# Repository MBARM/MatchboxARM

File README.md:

MatchboxARM
===========

CD content for MatchboxARM STM32F103C8T6 board and MatchboxARM robotic platform
    
    ## Software and design by Nedelcu Bogdan Sebastian.

To compile examplex for CooCox:
    * download CooCox
	* copy all "workspace" content from CD to "C:\CooCox\CoIDE\workspace"
	* install gcc-arm-none-eabi-4_6-2012q2-20120614.exe
Open CoIDE. In the menu -> project -> select toolchain path
set the pat to armgcc( C:\Program Files (x86)\GNU Tools ARM Embedded\4.6 2012q2\bin ).

To compile examples for KEIL, download KEIL evaluation version with 32kb limit.

The bootloader sources are in KEIL directory.

Most of the examples need NEED USB-TTL adapter to get the feedback.
You need to connect the adapter like this:

USB-TTL ADAPTER            MatchboxARM
    TX           ->         RX (PA10)
    RX           ->         TX (PA9)
    GND          ->         GND 

The setting on the PC side for the serial port are:
	   BAUD RATE : 38400 
	   DATA BITS : 8
	   STOP BITS : 1
	      PARITY : NONE
	FLOW CONTROL : NONE

The termite is a free serial terminal for Windows.

The work is still in progress for Linux.

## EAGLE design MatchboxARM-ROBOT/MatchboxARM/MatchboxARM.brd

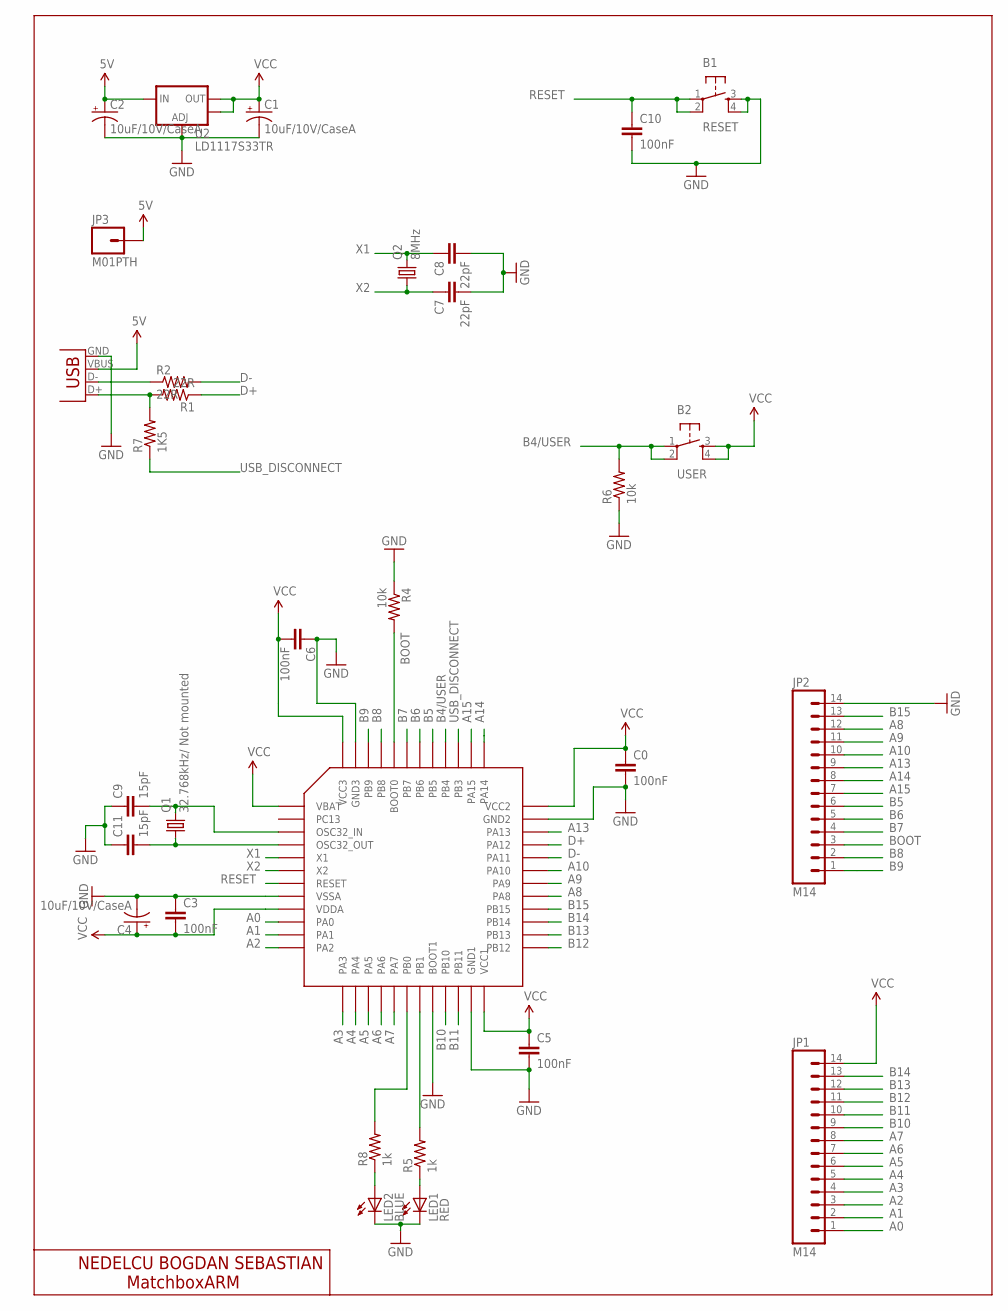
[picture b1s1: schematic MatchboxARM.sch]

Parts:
B1: RESET; TACTILE_SWITCH_SMD
B2: USER; TACTILE_SWITCH_SMD
C0, C3, C5, C6, C10: 100nF; 0603-CAP
C1, C2, C4: 10uF/10V/CaseA; EIA3216
C7, C8: 22pF; 0603-CAP
C9, C11: 15pF; 0603-CAP
JP1, JP2: M14; 1X14
JP3: M01PTH; 1X01
LED1: RED; LED-0603
LED2: BLUE; LED-0603
Q1: 32.768kHz/ Not mounted; TC26V
Q2: 8MHz; CTS406
R1, R2: 22R; 0603-RES
R4, R6: 10k; 0603-RES
R5, R8: 1k; 0603-RES
R7: 1K5; 0603-RES
U1: STM32F103CBT6; STM32F103CXT6
U2: LD1117S33TR; SOT223
USB1: miniUSBSMD; USB-MINIB

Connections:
5V: C2.A (+), JP3.1, U2.3 (IN), USB1.VBUS
A0: JP1.1, U1.10 (PA0)
A1: JP1.2, U1.11 (PA1)
A2: JP1.3, U1.12 (PA2)
A3: JP1.4, U1.13 (PA3)
A4: JP1.5, U1.14 (PA4)
A5: JP1.6, U1.15 (PA5)
A6: JP1.7, U1.16 (PA6)
A7: JP1.8, U1.17 (PA7)
A8: JP2.12, U1.29 (PA8)
A9: JP2.11, U1.30 (PA9)
A10: JP2.10, U1.31 (PA10)
A13: JP2.9, U1.34 (PA13)
A14: JP2.8, U1.37 (PA14)
A15: JP2.7, U1.38 (PA15)
B4/USER: B2.1, B2.2, R6.2, U1.40 (PB4)
B5: JP2.6, U1.41 (PB5)
B6: JP2.5, U1.42 (PB6)
B7: JP2.4, U1.43 (PB7)
B8: JP2.2, U1.45 (PB8)
B9: JP2.1, U1.46 (PB9)
B10: JP1.9, U1.21 (PB10)
B11: JP1.10, U1.22 (PB11)
B12: JP1.11, U1.25 (PB12)
B13: JP1.12, U1.26 (PB13)
B14: JP1.13, U1.27 (PB14)
B15: JP2.13, U1.28 (PB15)
BOOT: JP2.3, R4.2, U1.44 (BOOT0)
D+: R1.1, U1.33 (PA12)
D-: R2.2, U1.32 (PA11)
GND: B1.3, B1.4, C0.2, C1.C (-), C2.C (-), C3.1, C4.C (-), C5.2, C6.1, C7.2, C8.2, C9.1, C10.2, C11.1, JP2.14, LED1.C, LED2.C, R4.1, R6.1, U1.8 (VSSA), U1.20 (BOOT1), U1.23 (GND1), U1.35 (GND2), U1.47 (GND3), U2.1 (ADJ), USB1.GND
unnamed: R5.2, U1.19 (PB1)
unnamed: LED2.A, R8.1
unnamed: LED1.A, R5.1
unnamed: R8.2, U1.18 (PB0)
unnamed: C9.2, Q1.2, U1.3 (OSC32_IN)
unnamed: C11.2, Q1.1, U1.4 (OSC32_OUT)
unnamed: R2.1, USB1.D-
unnamed: R1.2, R7.2, USB1.D+
RESET: B1.1, B1.2, C10.1, U1.7 (RESET)
USB_DISCONNECT: R7.1, U1.39 (PB3)
VCC: B2.3, B2.4, C0.1, C1.A (+), C3.2, C4.A (+), C5.1, C6.2, JP1.14, U1.1 (VBAT), U1.9 (VDDA), U1.24 (VCC1), U1.36 (VCC2), U1.48 (VCC3), U2.2 (OUT), U2.4 (OUT)
X1: C8.1, Q2.3 (2), U1.5 (X1)
X2: C7.1, Q2.1, U1.6 (X2)

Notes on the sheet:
NEDELCU BOGDAN SEBASTIAN
MatchboxARM

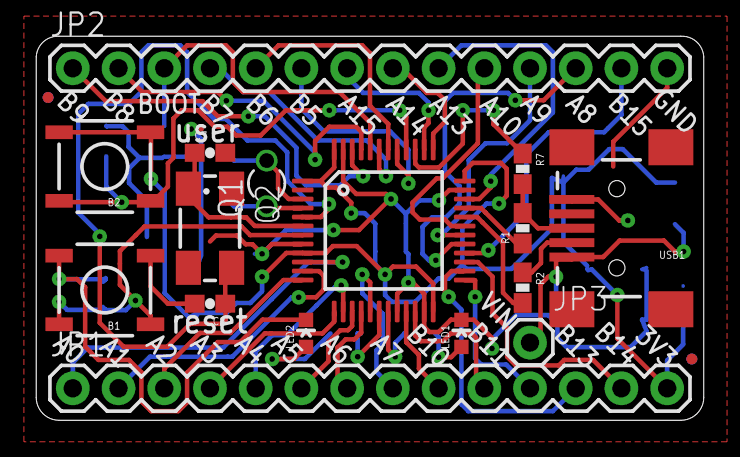
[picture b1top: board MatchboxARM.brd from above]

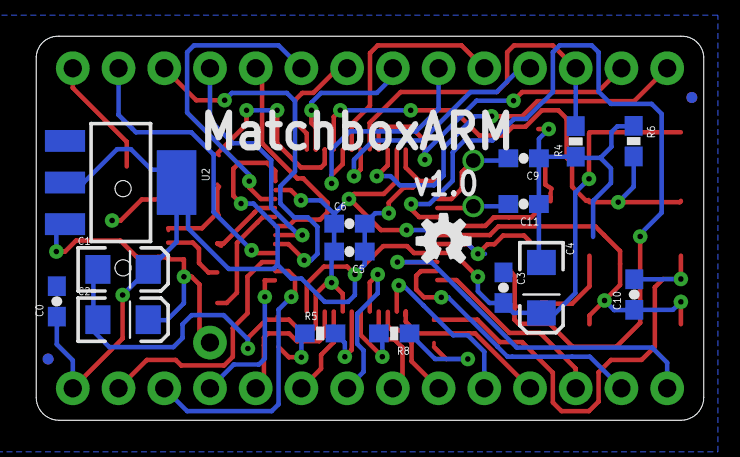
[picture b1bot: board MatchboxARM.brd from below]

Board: 2 copper layers, 37.1 x 21.3 mm, 33 parts (16 on the bottom side), 44 nets.

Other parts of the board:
U3: CREATIVE_COMMONS
U$4: OSHW-LOGOS; OSHW-LOGO-S

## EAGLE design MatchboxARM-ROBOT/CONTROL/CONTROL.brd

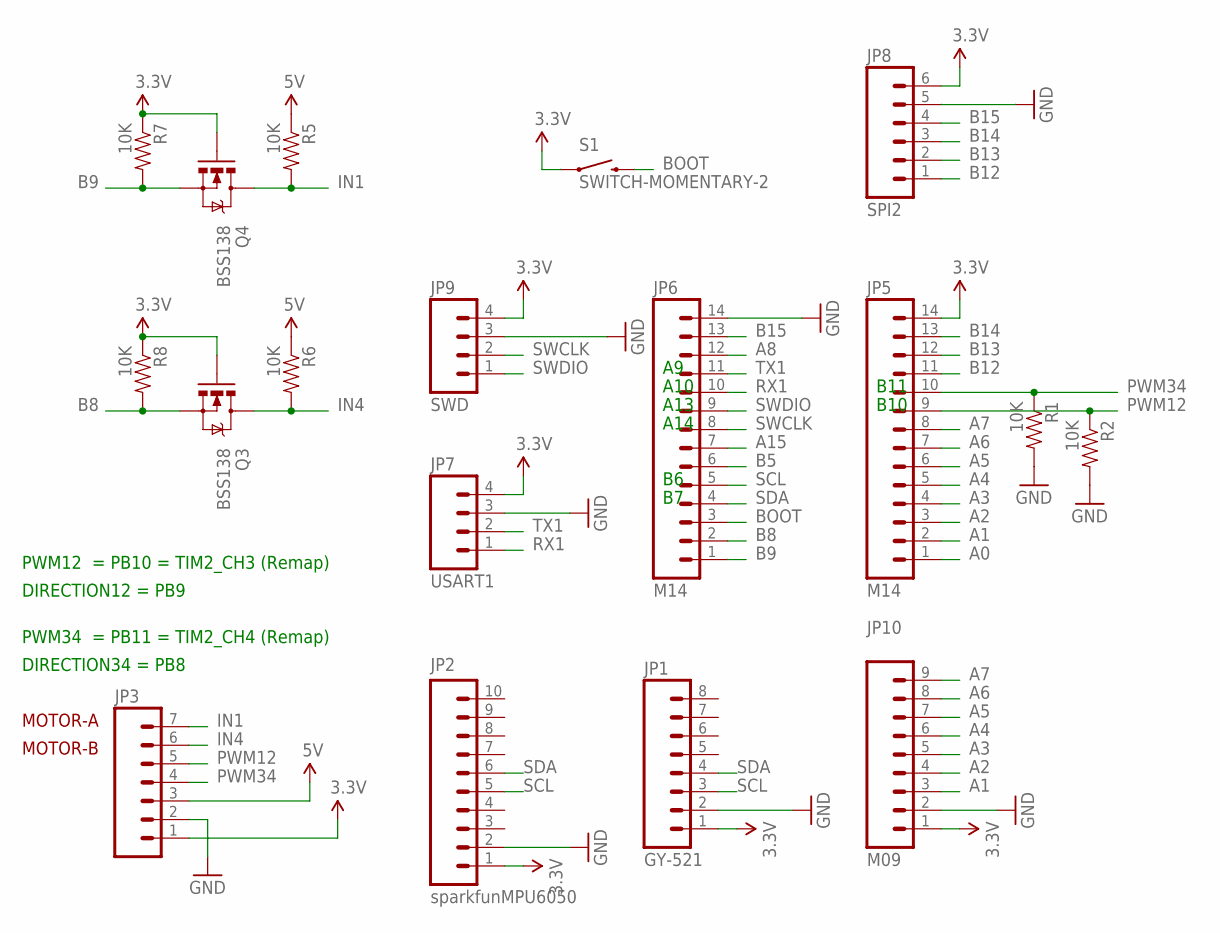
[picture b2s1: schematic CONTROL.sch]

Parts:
JP1: GY-521; 1X08
JP2: sparkfunMPU6050; 1X10
JP3: M07LONGPADS; 1X07_LONGPADS
JP5, JP6: M14; 1X14
JP7: USART1; 1X04
JP8: SPI2; 1X06
JP9: SWD; 1X04
JP10: M09; 1X09
Q3, Q4: BSS138; SOT23-3
R1, R2, R5, R6, R7, R8: 10K; 0805
S1: SWITCH-MOMENTARY-2; TACTILE_SWITCH_TALL

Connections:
3.3V: JP1.1, JP2.1, JP3.1, JP5.14, JP7.4, JP8.6, JP9.4, JP10.1, Q3.1 (G), Q4.1 (G), R7.1, R8.1, S1.A2 (1)
5V: JP3.3, R5.1, R6.1
A0: JP5.1
A1: JP5.2, JP10.3
A2: JP5.3, JP10.4
A3: JP5.4, JP10.5
A4: JP5.5, JP10.6
A5: JP5.6, JP10.7
A6: JP5.7, JP10.8
A7: JP5.8, JP10.9
A8: JP6.12
A15: JP6.7
B5: JP6.6
B8: JP6.2, Q3.2 (S), R8.2
B9: JP6.1, Q4.2 (S), R7.2
B12: JP5.11, JP8.1
B13: JP5.12, JP8.2
B14: JP5.13, JP8.3
B15: JP6.13, JP8.4
BOOT: JP6.3, S1.B2 (2)
GND: JP1.2, JP2.2, JP3.2, JP6.14, JP7.3, JP8.5, JP9.3, JP10.2, R1.2, R2.2
IN1: JP3.7, Q4.3 (D), R5.2
IN4: JP3.6, Q3.3 (D), R6.2
PWM12: JP3.5, JP5.9, R2.1
PWM34: JP3.4, JP5.10, R1.1
RX1: JP6.10, JP7.1
SCL: JP1.3, JP2.5, JP6.5
SDA: JP1.4, JP2.6, JP6.4
SWCLK: JP6.8, JP9.2
SWDIO: JP6.9, JP9.1
TX1: JP6.11, JP7.2

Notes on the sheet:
MOTOR-A
MOTOR-B
PWM12 = PB10 = TIM2_CH3 (Remap)
PWM34 = PB11 = TIM2_CH4 (Remap)
A13
A14
A10
DIRECTION12 = PB9
DIRECTION34 = PB8
B10
B11

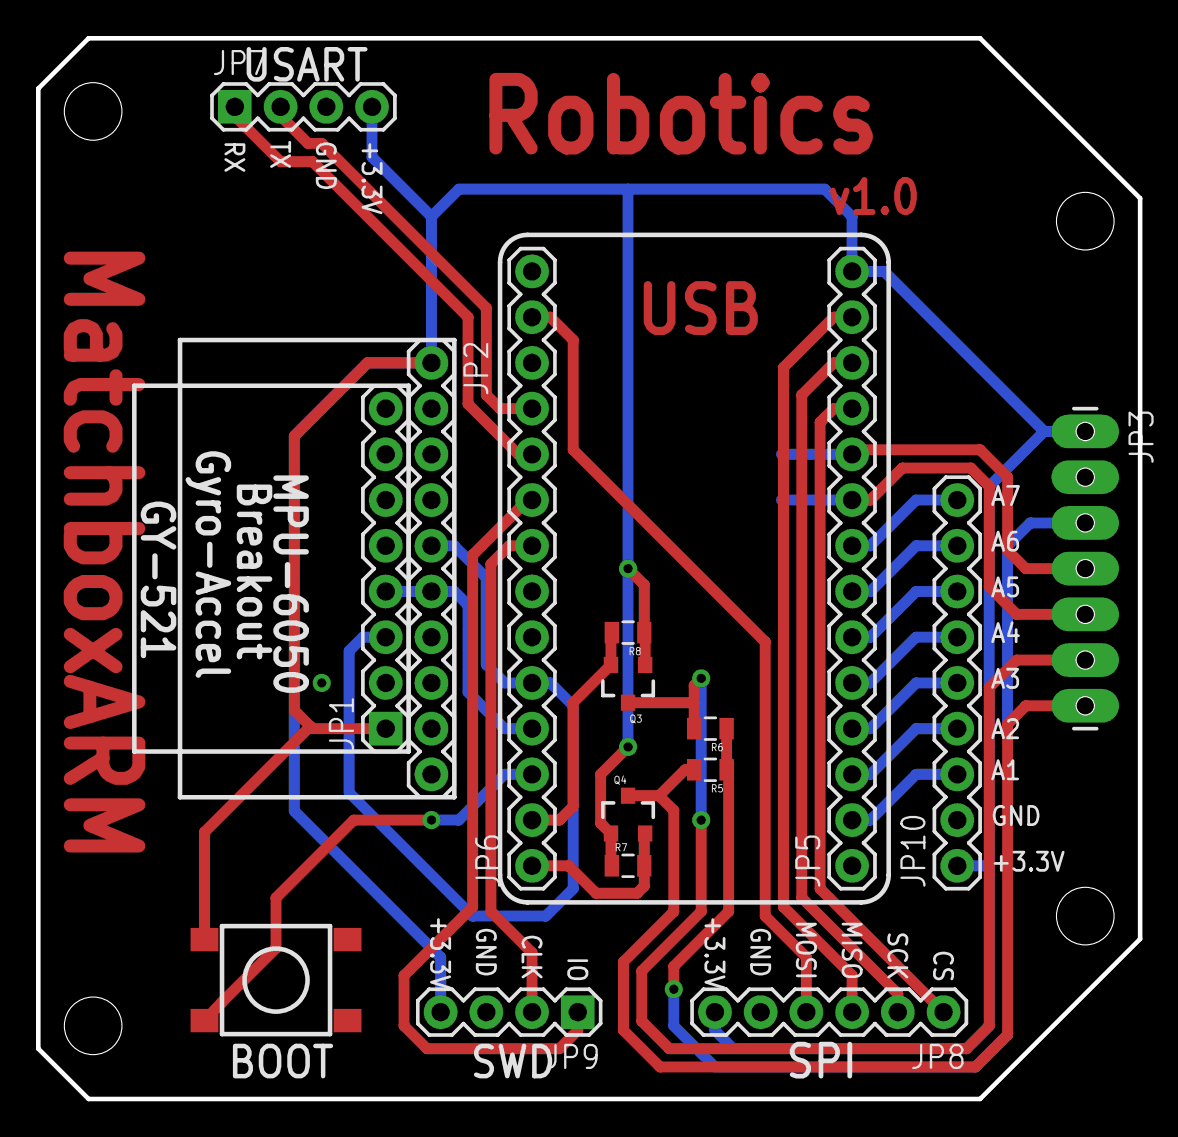
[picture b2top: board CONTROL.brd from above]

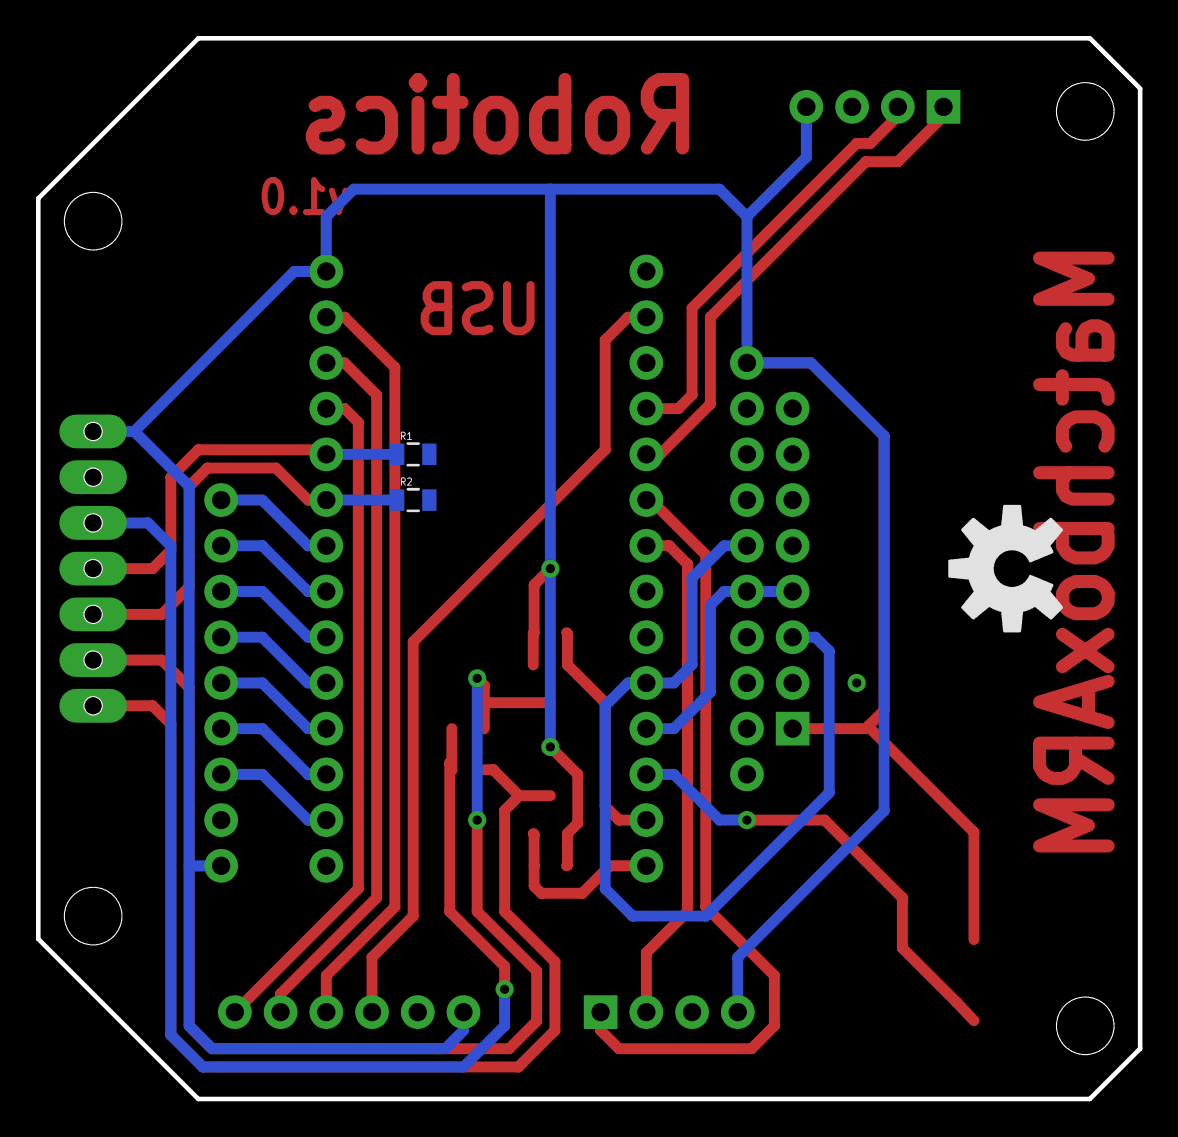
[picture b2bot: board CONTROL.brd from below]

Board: 2 copper layers, 61.2 x 58.9 mm, 20 parts (3 on the bottom side), 27 nets.

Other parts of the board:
U$1: OSHW-LOGO-L
U$2: CREATIVE_COMMONS

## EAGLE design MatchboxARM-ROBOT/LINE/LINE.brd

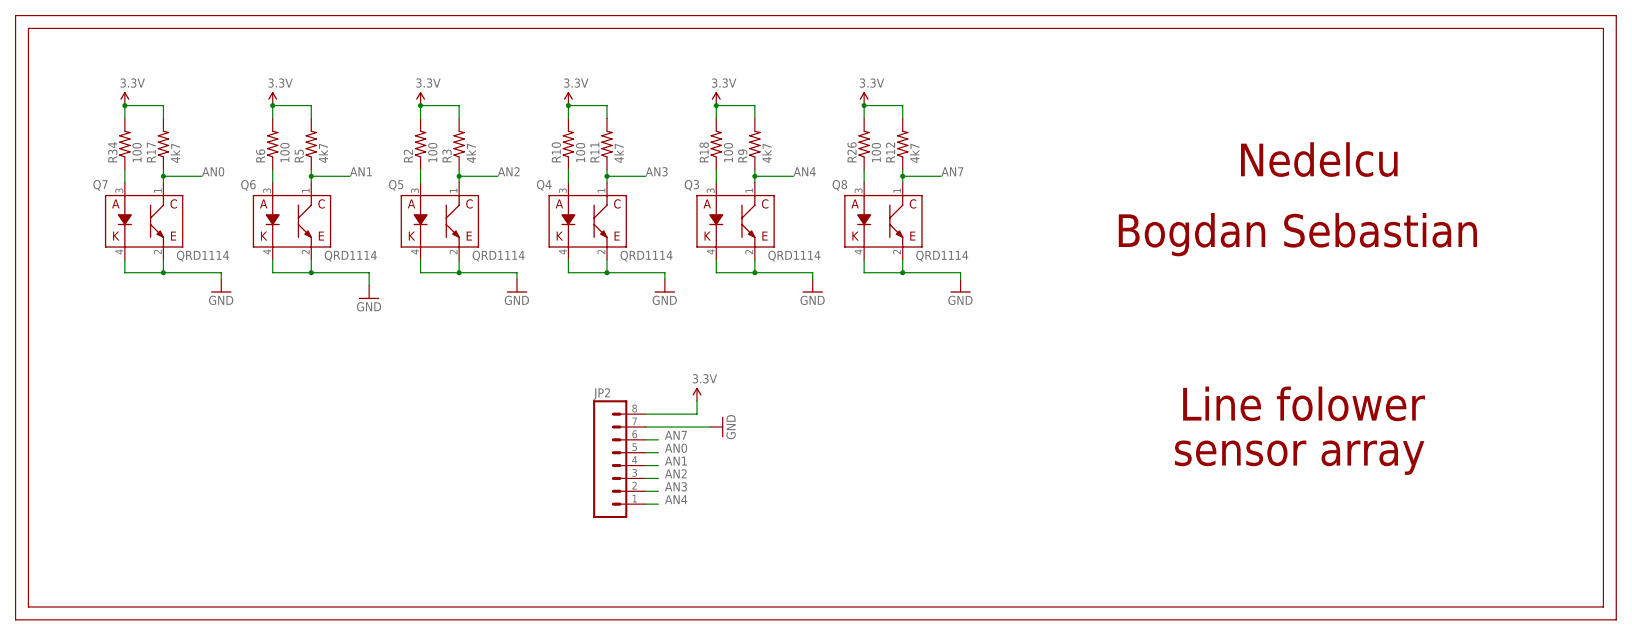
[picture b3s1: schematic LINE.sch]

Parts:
JP2: M081X08; 1X08
Q3, Q4, Q5, Q6, Q7, Q8: QRD1114
R2, R6, R10, R18, R26, R34: 100; 0805
R3, R5, R9, R11, R12, R17: 4k7; 0805

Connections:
3.3V: JP2.8, R2.2, R3.2, R5.2, R6.2, R9.2, R10.2, R11.2, R12.2, R17.2, R18.2, R26.2, R34.2
AN0: JP2.5, Q7.1 (E), R17.1
AN1: JP2.4, Q6.1 (E), R5.1
AN2: JP2.3, Q5.1 (E), R3.1
AN3: JP2.2, Q4.1 (E), R11.1
AN4: JP2.1, Q3.1 (E), R9.1
AN7: JP2.6, Q8.1 (E), R12.1
GND: JP2.7, Q3.2 (C), Q3.4 (K), Q4.2 (C), Q4.4 (K), Q5.2 (C), Q5.4 (K), Q6.2 (C), Q6.4 (K), Q7.2 (C), Q7.4 (K), Q8.2 (C), Q8.4 (K)
unnamed: Q8.3 (A), R26.1
unnamed: Q7.3 (A), R34.1
unnamed: Q6.3 (A), R6.1
unnamed: Q5.3 (A), R2.1
unnamed: Q3.3 (A), R18.1
unnamed: Q4.3 (A), R10.1

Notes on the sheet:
Nedelcu
Bogdan Sebastian
Line folower
sensor array

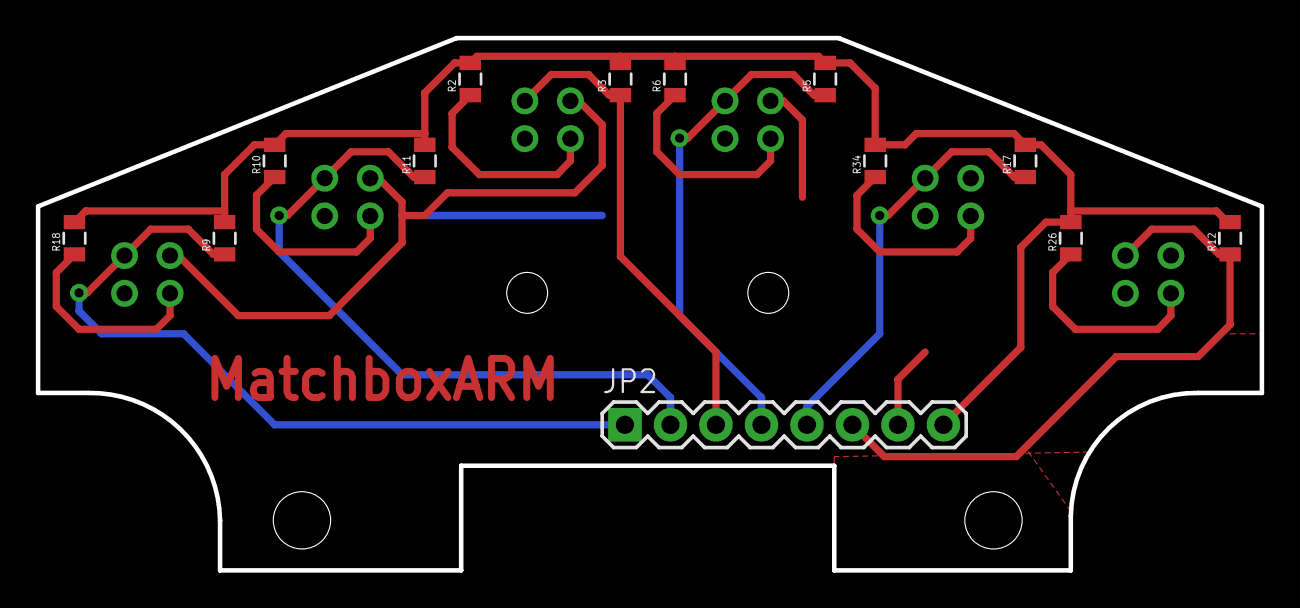
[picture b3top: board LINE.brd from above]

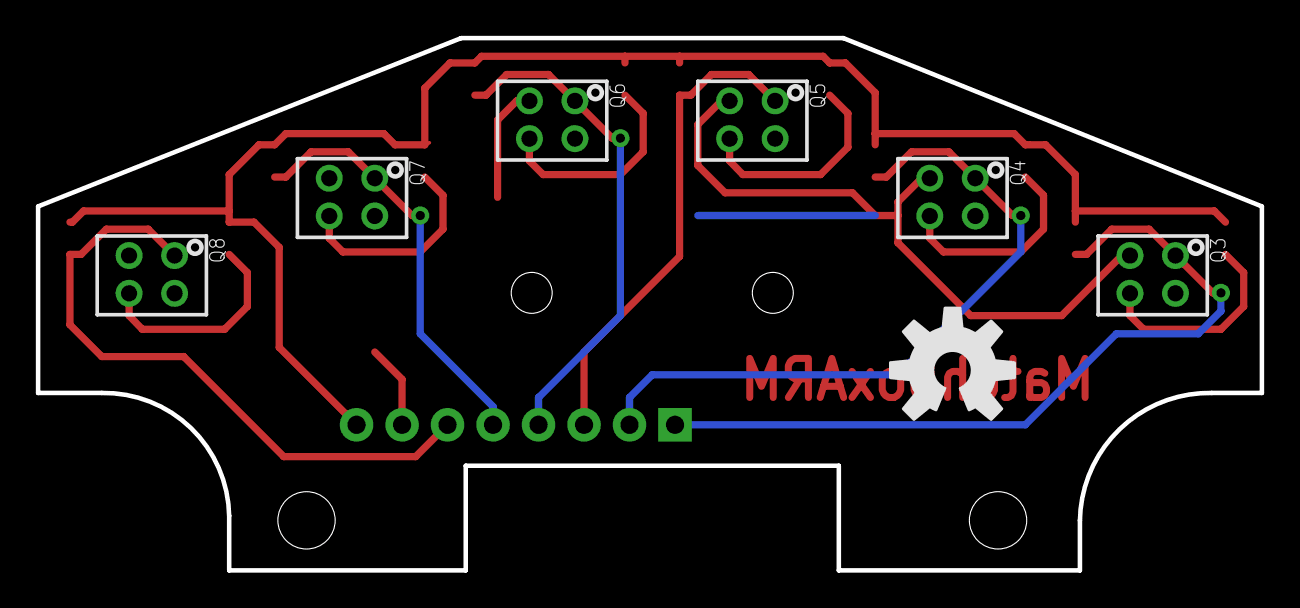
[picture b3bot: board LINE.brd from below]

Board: 2 copper layers, 68.3 x 29.7 mm, 21 parts (7 on the bottom side), 14 nets.

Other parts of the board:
U$1: CREATIVE_COMMONS
U$2: OSHW-LOGO-L

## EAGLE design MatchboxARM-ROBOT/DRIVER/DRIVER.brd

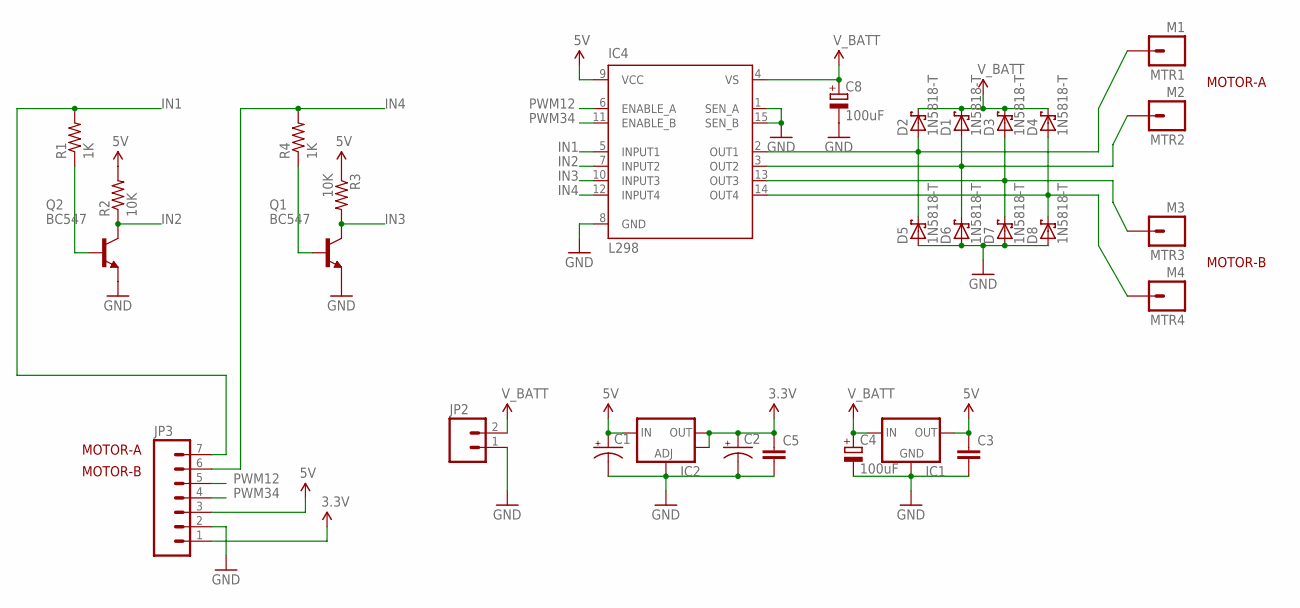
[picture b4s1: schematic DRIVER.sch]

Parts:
C1, C2: CAP_POL1206-KIT; EIA3216-KIT
C3: CAPPTH; CAP-PTH-SMALL
C4, C8: 100uF; E2,5-5
C5: CAP0805; 0805
D1, D2, D3, D4, D5, D6, D7, D8: 1N5818-T; DO41-7.6
IC1: V_REG_78XX-TO-220; TO-220-ALT
IC2: V_REG_LM1117SOT223; SOT223
IC4: L298; MULTIWATT-15
JP2: M02LOCK_LONGPADS; 1X02_LOCK_LONGPADS
JP3: M07LONGPADS; 1X07_LONGPADS
MTR1: M1; 1X01_LONGPAD
MTR2: M2; 1X01_LONGPAD
MTR3: M3; 1X01_LONGPAD
MTR4: M4; 1X01_LONGPAD
Q1, Q2: BC547; TO92
R1, R4: 1K; 0805
R2, R3: 10K; 0805

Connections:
3.3V: C2.A (+), C5.1, IC2.2 (OUT), IC2.4 (OUT), JP3.1
5V: C1.A (+), C3.1, IC1.OUT, IC2.3 (IN), IC4.9 (VCC), JP3.3, R2.2, R3.1
GND: C1.C (-), C2.C (-), C3.2, C4.-, C5.2, C8.-, D5.A, D6.A, D7.A, D8.A, IC1.GND, IC2.1 (ADJ), IC4.1 (SEN_A), IC4.8 (GND), IC4.15 (SEN_B), JP2.1, JP3.2, Q1.1 (E), Q2.1 (E)
IN1: IC4.5 (INPUT1), JP3.7, R1.2
IN2: IC4.7 (INPUT2), Q2.3 (C), R2.1
IN3: IC4.10 (INPUT3), Q1.3 (C), R3.2
IN4: IC4.12 (INPUT4), JP3.6, R4.2
unnamed: Q2.2 (B), R1.1
unnamed: Q1.2 (B), R4.1
unnamed: D2.A, D5.C, IC4.2 (OUT1), MTR1.1
unnamed: D1.A, D6.C, IC4.3 (OUT2), MTR2.1
unnamed: D3.A, D7.C, IC4.13 (OUT3), MTR3.1
unnamed: D4.A, D8.C, IC4.14 (OUT4), MTR4.1
PWM12: IC4.6 (ENABLE_A), JP3.5
PWM34: IC4.11 (ENABLE_B), JP3.4
V_BATT: C4.+, C8.+, D1.C, D2.C, D3.C, D4.C, IC1.IN, IC4.4 (VS), JP2.2

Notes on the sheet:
MOTOR-A
MOTOR-B

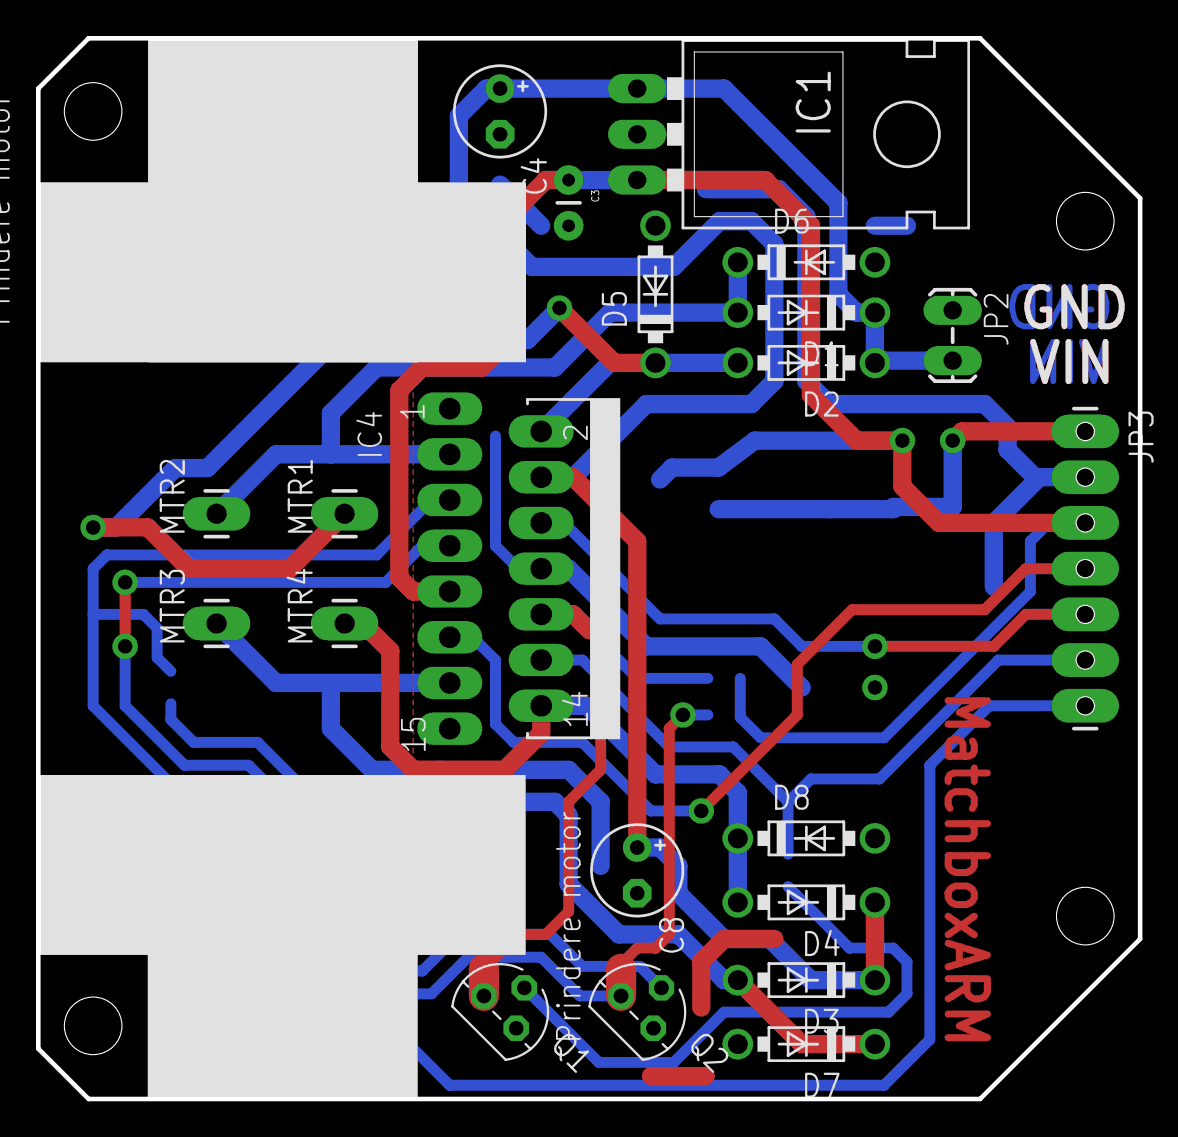
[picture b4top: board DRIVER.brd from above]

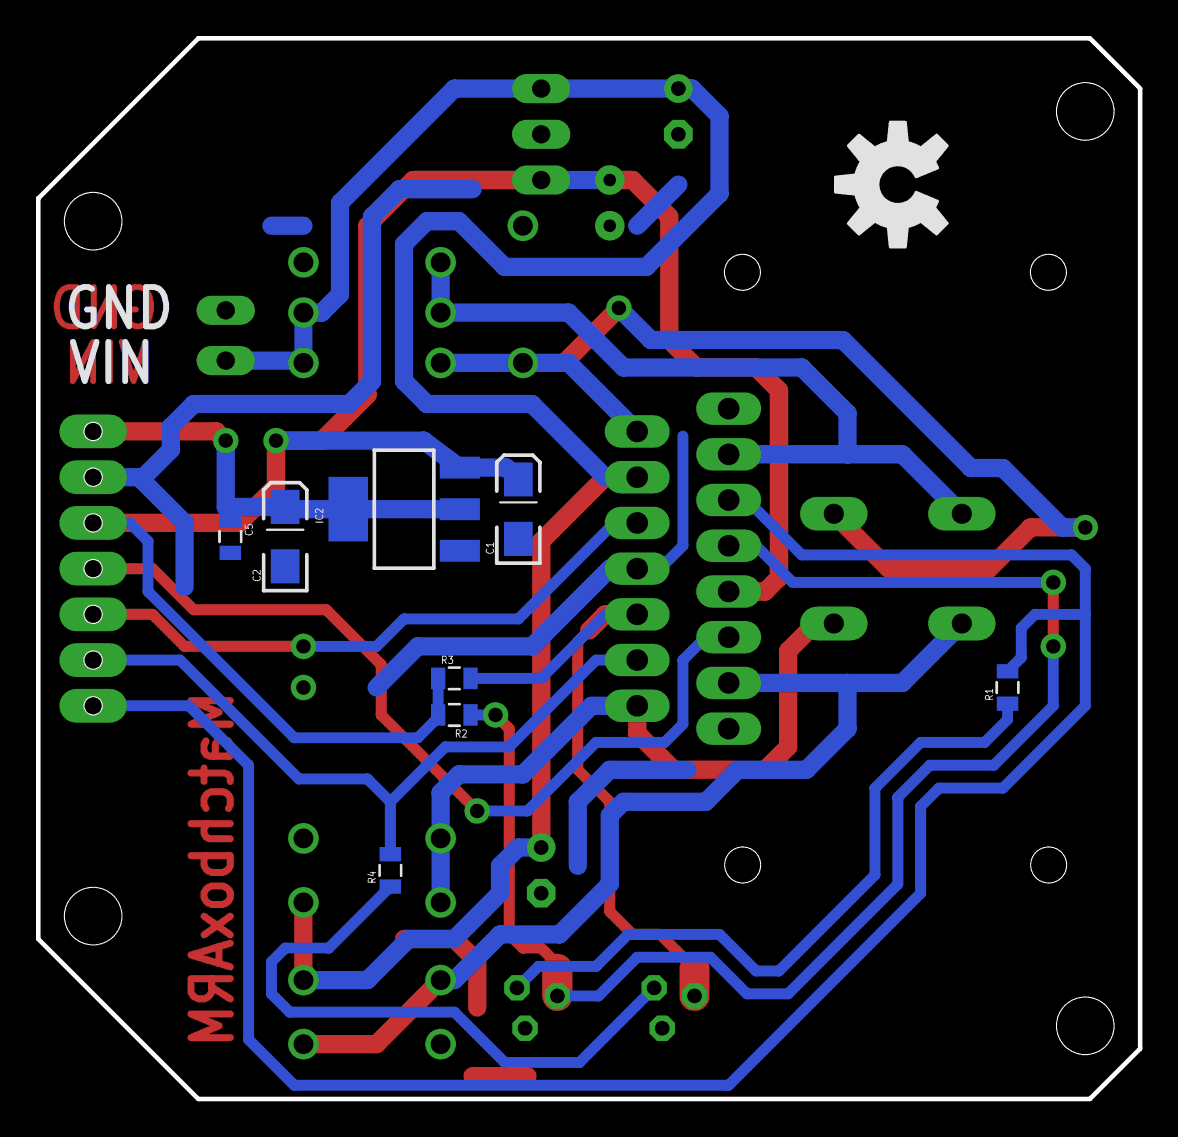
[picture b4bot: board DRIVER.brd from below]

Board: 2 copper layers, 61.2 x 58.9 mm, 33 parts (9 on the bottom side), 16 nets.

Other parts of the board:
U$1, U$3: MOTOR
U$13: OSHW-LOGO-L
U$14: CREATIVE_COMMONS

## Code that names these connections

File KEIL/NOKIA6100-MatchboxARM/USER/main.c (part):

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 * Compiler: Keil-MDK 4.50.0.0
 *
 * MatchboxARM    LCD Nokia-6100
 *    PB13               CS
 *    PB10              SCLK
 *    PB11              SDATA
 *    PB12              RESET
 *    VCC               VCC
 *    GND               GND
 *                      VLCD NEEDS EXTERNALL 6-7V.                   
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
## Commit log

2014-01-29 MatchboxARM CD
2016-04-02 Modbus example
    Modbus example using FreeModbus library
2016-04-02 Cleaning the Modbus project
    Cleaning the Modbus project
2016-04-02 Added dipswitch reading example
    Read 3 contacts dipswitch using only one pin
2016-04-16 New Modbus example with request check
    Modbus example with request check.
    One led blink for each loop, and the other one only if we have Modbus
    connection with a master that request data.
2016-04-16 USART3 example
    USART3 example
2016-04-16 SysTick not needed
2016-05-03 Blink consecutively all the pins of the MatchboxARM
    This example blink consecutively all the pins of the MatchboxARM,
    so we can check short-free functionality.
2016-08-07 New example that update holding registers, input registers, and coils
    This example update previous modbus example with request event check by
    blinking a LED and adds also updating of dataspaces for holding
    registers, input registers and coils. Also we have a description of how
    to use modbuspoll utility
    to poll registers to see how data modify in realtime, and also how to
    read registers when using the RTU->TCP adapter from ICPDAS.

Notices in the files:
KEIL/NOKIA6100-MatchboxARM/USER/main.c:
Copyright 2013-2014 Nedelcu Bogdan Sebastian
This program is free software: you can redistribute it and/or modify
it under the terms of the GNU Lesser General Public License as published
parts and their libraries:
SparkFun-Connectors: Licensing: CC v3.0 Share-Alike You are welcome to use this library for commercial purposes.
SparkFun-Aesthetics: Released under the Creative Commons Attribution Share-Alike 3.0 License
SparkFun-Aesthetics: http://creativecommons.org/licenses/by-sa/3.0
